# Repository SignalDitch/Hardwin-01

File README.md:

# Hardwin-01
Arduino compatible dev board

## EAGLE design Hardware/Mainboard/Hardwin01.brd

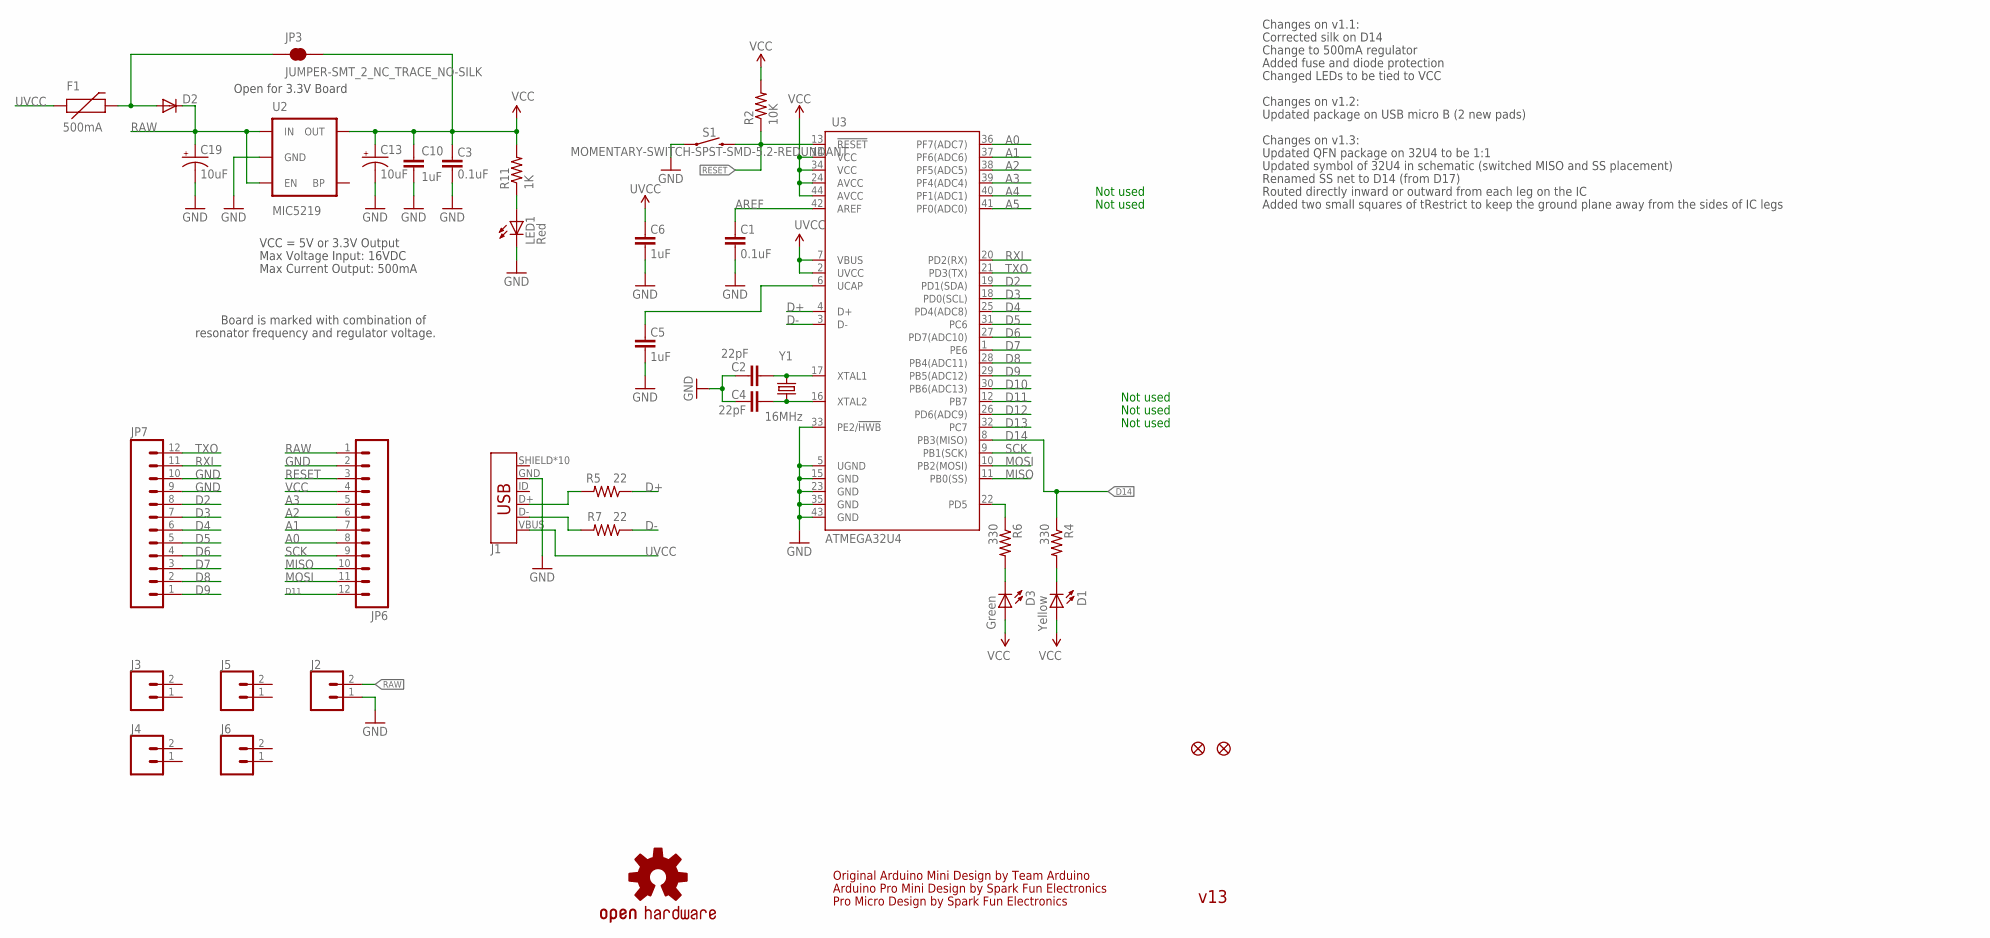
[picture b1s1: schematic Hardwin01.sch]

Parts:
C1, C3: 0.1uF; 0603-CAP
C2, C4: 22pF; 0603-CAP
C5, C6, C10: 1uF; 0603-CAP
C13, C19: 10uF; EIA3216
D1: Yellow; LED-0603
D2: DIODESOD; SOD-323
D3: Green; LED-0603
F1: 500mA; PTC-1206
J1: USB_MICRO-B_HALF_PTH_MILL; USB-MICROB-PTH-MILL
J2: CONN_02PTH3; 1X02_LONGPADS
J3, J4, J5, J6: CONN_02; 1X02
JP1, JP2: FIDUCIALUFIDUCIAL; MICRO-FIDUCIAL
JP3: JUMPER-SMT_2_NC_TRACE_NO-SILK; SMT-JUMPER_2_NC_TRACE_NO-SILK
JP6, JP7: M12PTH; 1X12
LED1: Red; LED-0603
R2: 10K; 0603-RES
R4, R6: 330; 0603-RES
R5, R7: 22; 0603-RES
R11: 1K; 0603-RES
S1: MOMENTARY-SWITCH-SPST-SMD-5.2-REDUNDANT; TACTILE_SWITCH_SMD_5.2MM
U2: MIC5219; SOT23-5
U3: ATMEGA32U4; QFN-44-NOPAD_1:1-OUTFAKES
U$3: OSHW-LOGOS; OSHW-LOGO-S
Y1: 16MHz; CRYSTAL-SMD-5X3

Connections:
A0: JP6.8, U3.36 (PF7(ADC7))
A1: JP6.7, U3.37 (PF6(ADC6))
A2: JP6.6, U3.38 (PF5(ADC5))
A3: JP6.5, U3.39 (PF4(ADC4))
A4: U3.40 (PF1(ADC1))
A5: U3.41 (PF0(ADC0))
AREF: C1.2, U3.42 (AREF)
D2: JP7.8, U3.19 (PD1(SDA))
D3: JP7.7, U3.18 (PD0(SCL))
D4: JP7.6, U3.25 (PD4(ADC8))
D5: JP7.5, U3.31 (PC6)
D6: JP7.4, U3.27 (PD7(ADC10))
D7: JP7.3, U3.1 (PE6)
D8: JP7.2, U3.28 (PB4(ADC11))
D9: JP7.1, U3.29 (PB5(ADC12))
D10: U3.30 (PB6(ADC13))
D11: JP6.12, U3.12 (PB7)
D12: U3.26 (PD6(ADC9))
D13: U3.32 (PC7)
D14: R4.1, U3.8 (PB3(MISO))
D+: R5.1, U3.4 (D+)
D-: R7.1, U3.3 (D-)
GND: C1.1, C2.2, C3.1, C4.2, C5.1, C6.1, C10.2, C13.C (-), C19.C (-), J1.GND, J2.1, JP6.2, JP7.9, JP7.10, LED1.C, S1.1, S1.2 (1), U2.2 (GND), U3.5 (UGND), U3.15 (GND), U3.23 (GND), U3.33 (PE2/!HWB), U3.35 (GND), U3.43 (GND)
MISO: JP6.10, U3.11 (PB0(SS))
MOSI: JP6.11, U3.10 (PB2(MOSI))
unnamed: C4.1, U3.16 (XTAL2), Y1.1
unnamed: C2.1, U3.17 (XTAL1), Y1.3 (2)
unnamed: D2.2 (A), F1.2, JP3.1
unnamed: C5.2, U3.6 (UCAP)
unnamed: D1.C, R4.2
unnamed: J1.D-, R7.2
unnamed: D3.C, R6.2
unnamed: J1.D+, R5.2
unnamed: LED1.A, R11.1
RAW: C19.A (+), D2.1 (C), J2.2, JP6.1, U2.1 (IN), U2.3 (EN)
RESET: JP6.3, R2.1, S1.3 (2), S1.4 (2), U3.13 (!RESET)
RXI: JP7.11, U3.20 (PD2(RX))
SCK: JP6.9, U3.9 (PB1(SCK))
TXLED: R6.1, U3.22 (PD5)
TXO: JP7.12, U3.21 (PD3(TX))
UVCC: C6.2, F1.1, J1.VBUS, U3.2 (UVCC), U3.7 (VBUS)
VCC: C3.2, C10.1, C13.A (+), D1.A, D3.A, JP3.2, JP6.4, R2.2, R11.2, U2.5 (OUT), U3.14 (VCC), U3.24 (AVCC), U3.34 (VCC), U3.44 (AVCC)

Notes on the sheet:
Original Arduino Mini Design by Team Arduino
Arduino Pro Mini Design by Spark Fun Electronics
Max Voltage Input: 16VDC
Max Current Output: 500mA
Board is marked with combination of
resonator frequency and regulator voltage.
VCC = 5V or 3.3V Output
Not used
Pro Micro Design by Spark Fun Electronics
Changes on v1.1:
Corrected silk on D14
Change to 500mA regulator
Open for 3.3V Board
Added fuse and diode protection
Changed LEDs to be tied to VCC
Changes on v1.2:
Updated package on USB micro B (2 new pads)
Changes on v1.3:
Updated QFN package on 32U4 to be 1:1
Updated symbol of 32U4 in schematic (switched MISO and SS placement)
Renamed SS net to D14 (from D17)
Routed directly inward or outward from each leg on the IC
Added two small squares of tRestrict to keep the ground plane away from the sides of IC legs
v13

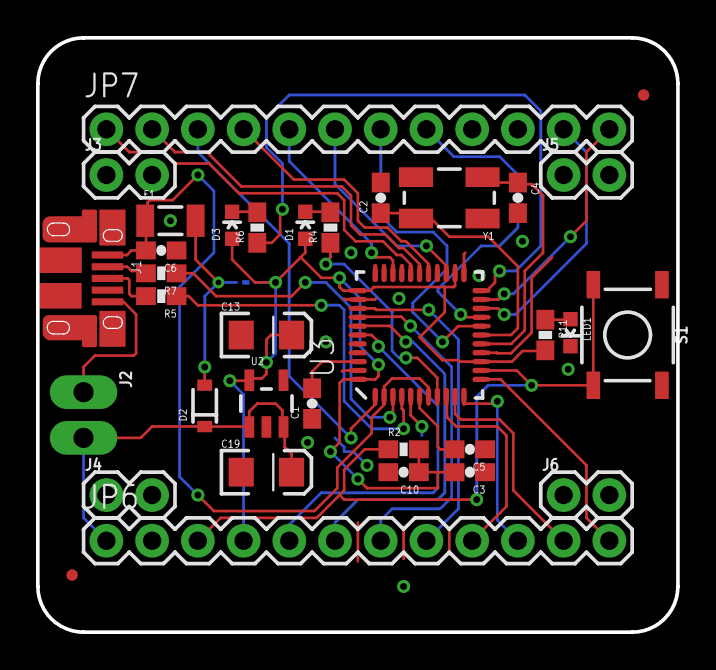
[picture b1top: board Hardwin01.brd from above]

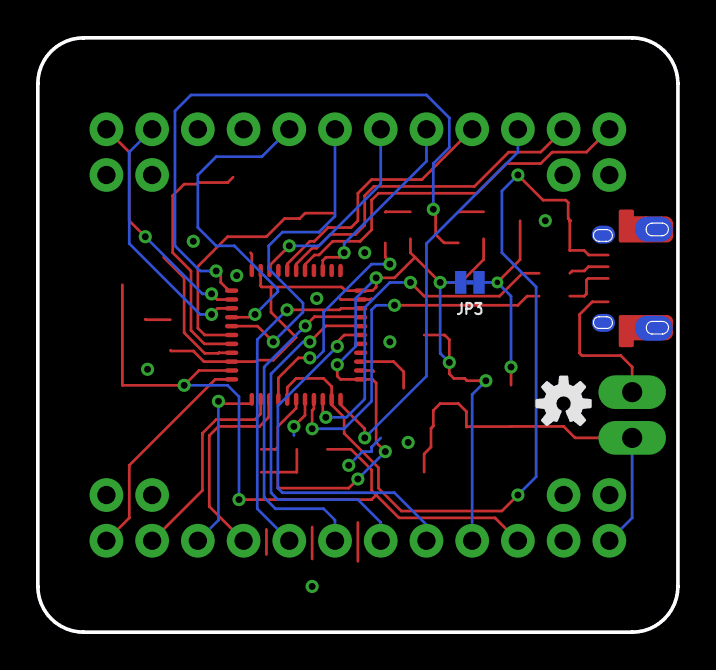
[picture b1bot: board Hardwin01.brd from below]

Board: 2 copper layers, 35.6 x 33.0 mm, 36 parts (2 on the bottom side), 37 nets.

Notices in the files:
parts and their libraries:
SparkFun-Connectors: Licensing: Creative Commons ShareAlike 4.0 International - https://creativecommons.org/licenses/by-sa/4.0
